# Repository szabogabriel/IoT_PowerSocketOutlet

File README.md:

# IoT_PowerSocketOutlet
A simple IoT device based on NodeMCU with ESP-8266.

The aim of this project was to test out several concepts and technologies, like IoT with MQTT communication and embedded computing via Node MCU (ESP-8266).

The wiring diagrams were done using KiCad.

## Functionalities

The device has four power socket outlets. Every socket has an LED indicator whether it is turned off or on and also a switch to turn it on or off. The software connects to an MQTT server, where it can be controlled (turn specific power sockets on or off) and request the status of the ports.

## Hardware

The main computing is performed by the Node MCU (ESP-8266) microcomputer. It is paired with a 4-way relay module and a power supply module (220V AC to 5V DC).

The only custom wiring is a low pass filter for the push buttons and was done on a prototyping board. I prefer a low pass filter for the debounce instead of a software implementation, altough, it is not a perfect solution.

The indicator LEDs are connected to the relay module's selector input. This way there is no need to maintain separate ports for the LEDs and the selectors.

The external power supply is connected both to the Node MCU (via the VIN and G ports) and the relay board. The relays need 5V to be able to operate, and the Node MCU is only able to provide 3.3V which is sufficient for the switching impulse, but not for powering the relays.

## Software

The software was done via the Arduino IDE. It uses the [PubSubClient](https://www.arduino.cc/reference/en/libraries/pubsubclient) and the [ESP8266WiFi](https://github.com/esp8266/Arduino/tree/master/libraries/ESP8266WiFi) libraries. The code builds upon the PubSubClient example. It holds the state of the ports (on/off) thus eliminating unneccessary `digitalWrite()` calls.

Node MCU needs to maintain the HTTP stack in the background. This is made sure via the `yield()` function, which is implicitely called each time before entering the `loop()` function. A problem occures, when the computation takes too long (for example because of `delay()` calls). In that case, the Node MCU reaches a timeout and performs a reset. To omit this, the code is 'polluted' with explicit `yield()` calls.

## Protocol

A simple protocol based on MQTT was implemented. There are two separate topics persent:

* /cord/update
* /cord/status

### `/cord/update`

This topic is used to send commands to the software. The possible commands consist of the following convention: `[port] [ON|OFF]` or the `STATUS` command. After each update the status of the device is published.

### `/cord/status`

Used by the device to publish its current status in a JSON format. 

## Test environemnt

The device was tested by using a [Mosquitto](https://mosquitto.org/) server running on an [OpenWRT](https://openwrt.org/) router on a separate IoT WiFi network.

## Todo

The communication protocol isn't a standardized format. It produces a JSON for the status message, but it doesn't accept one.

Should two separate messages be fetched in a short period of time, it sometimes hangs. Thus a delay of a few hundred milliseconds between command messages is a must.

## Images

!(Front view)[/pictures/01_front.jpg]

!(Back view)[/pictures/02_back.jpg]

!(Inside view)[/pictures/03_inside.jpg]

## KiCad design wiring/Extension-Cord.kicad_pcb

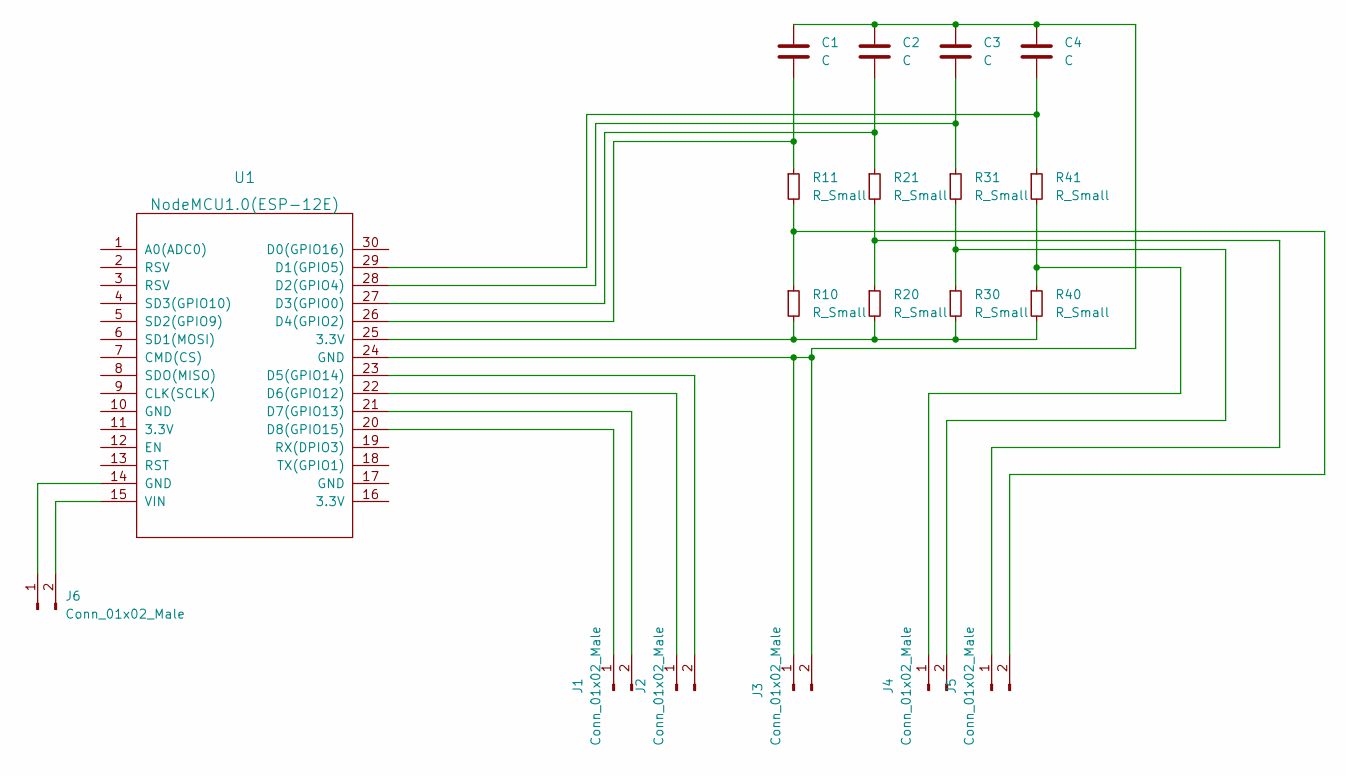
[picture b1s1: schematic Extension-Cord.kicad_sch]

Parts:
C1, C2, C3, C4: C; C_Disc_D5.0mm_W2.5mm_P2.50mm
J1, J2, J3, J4, J5, J6: Conn_01x02_Male; PinSocket_2x01_P2.00mm_Vertical
R10, R11, R20, R21, R30, R31, R40, R41: R_Small; R_Axial_DIN0204_L3.6mm_D1.6mm_P5.08mm_Horizontal
U1: NodeMCU1.0(ESP-12E); NodeMCU1.0(12-E)

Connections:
unnamed: C1.1, C2.1, C3.1, C4.1, J3.1, J3.2, U1.24 (GND)
unnamed: C1.2, R11.1, U1.26 (D4(GPIO2))
unnamed: C2.2, R21.1, U1.27 (D3(GPIO0))
unnamed: C3.2, R31.1, U1.28 (D2(GPIO4))
unnamed: C4.2, R41.1, U1.29 (D1(GPIO5))
unnamed: J1.1, U1.20 (D8(GPIO15))
unnamed: J1.2, U1.21 (D7(GPIO13))
unnamed: J2.1, U1.22 (D6(GPIO12))
unnamed: J2.2, U1.23 (D5(GPIO14))
unnamed: J6.1, U1.14 (GND)
unnamed: J6.2, U1.15 (VIN)
unnamed: J5.2, R10.1, R11.2
unnamed: R10.2, R20.2, R30.2, R40.2, U1.25 (3.3V)
unnamed: J5.1, R20.1, R21.2
unnamed: J4.2, R30.1, R31.2
unnamed: J4.1, R40.1, R41.2

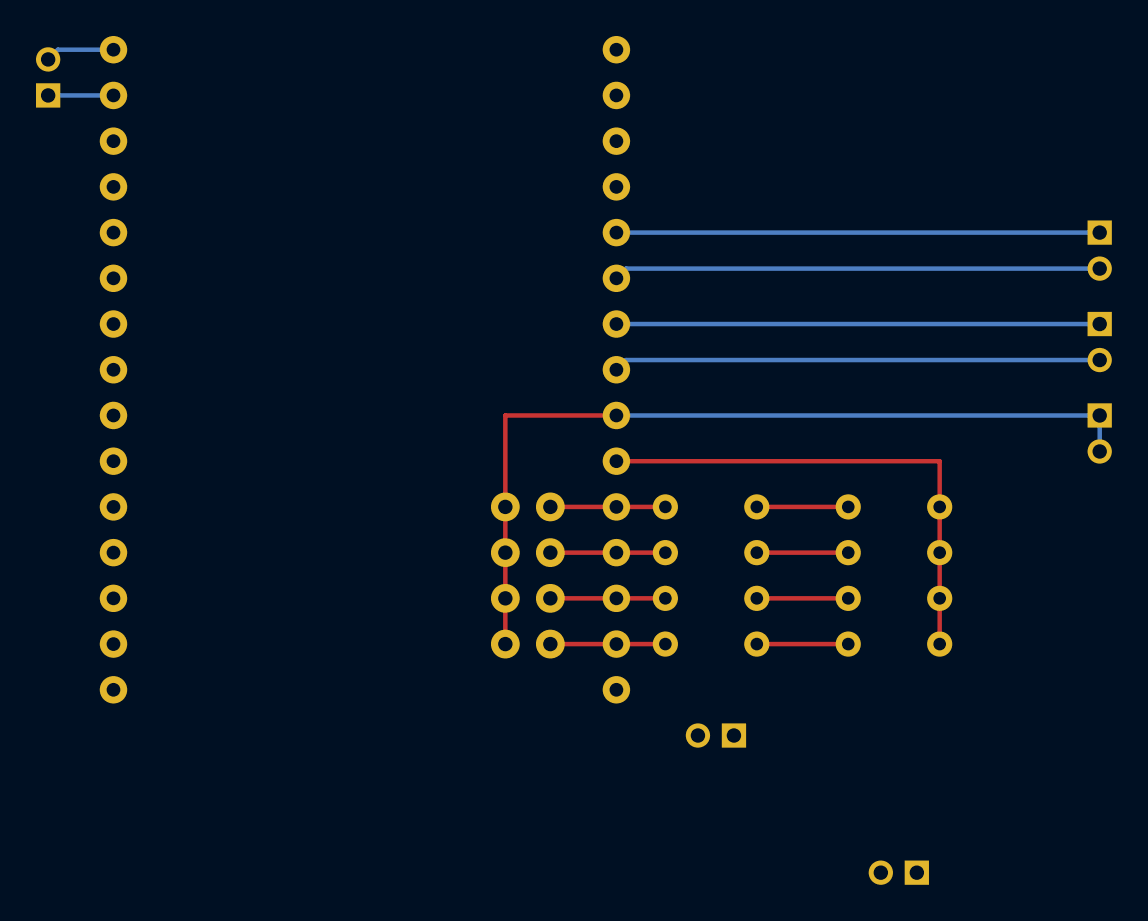
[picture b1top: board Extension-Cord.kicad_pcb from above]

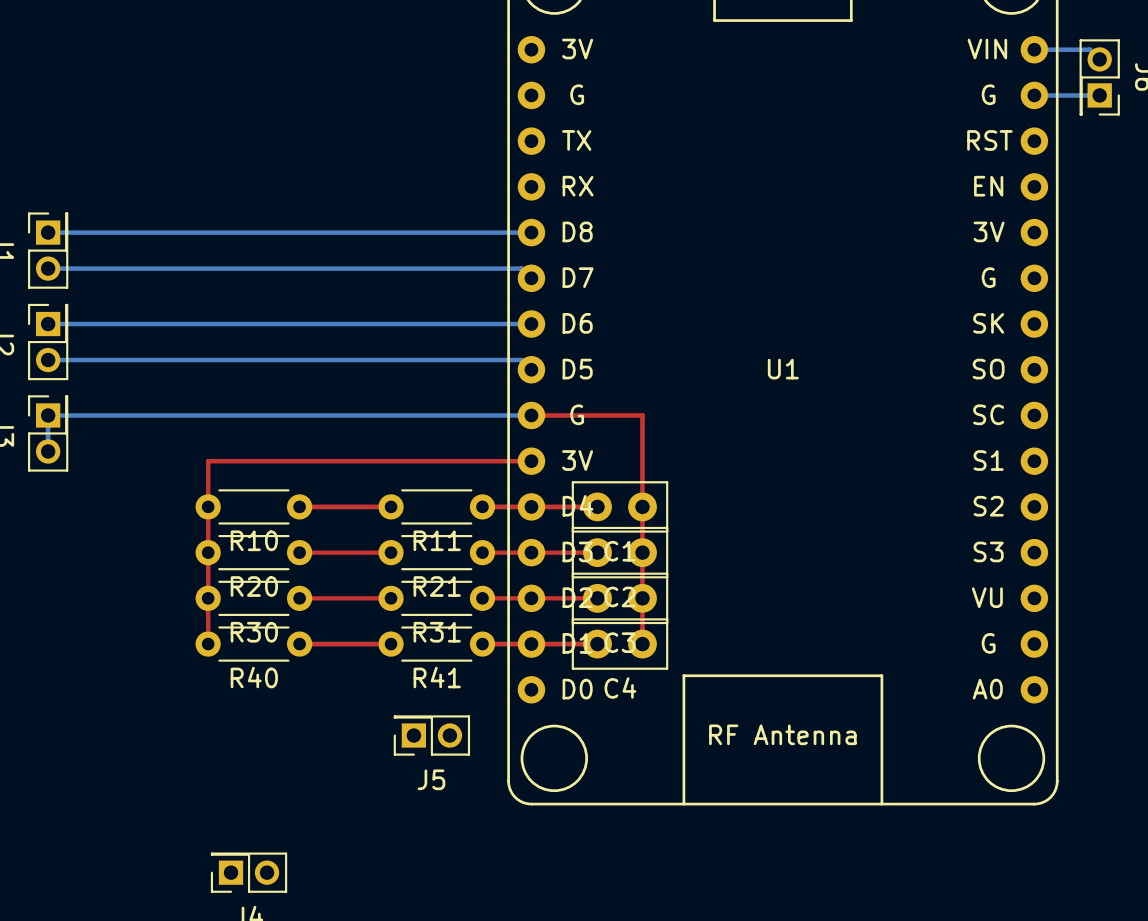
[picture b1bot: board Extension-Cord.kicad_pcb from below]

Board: 2 copper layers, 19 parts (19 on the bottom side), 16 nets.

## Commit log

2023-01-01 Add a util script
2023-01-01 Pictures added
